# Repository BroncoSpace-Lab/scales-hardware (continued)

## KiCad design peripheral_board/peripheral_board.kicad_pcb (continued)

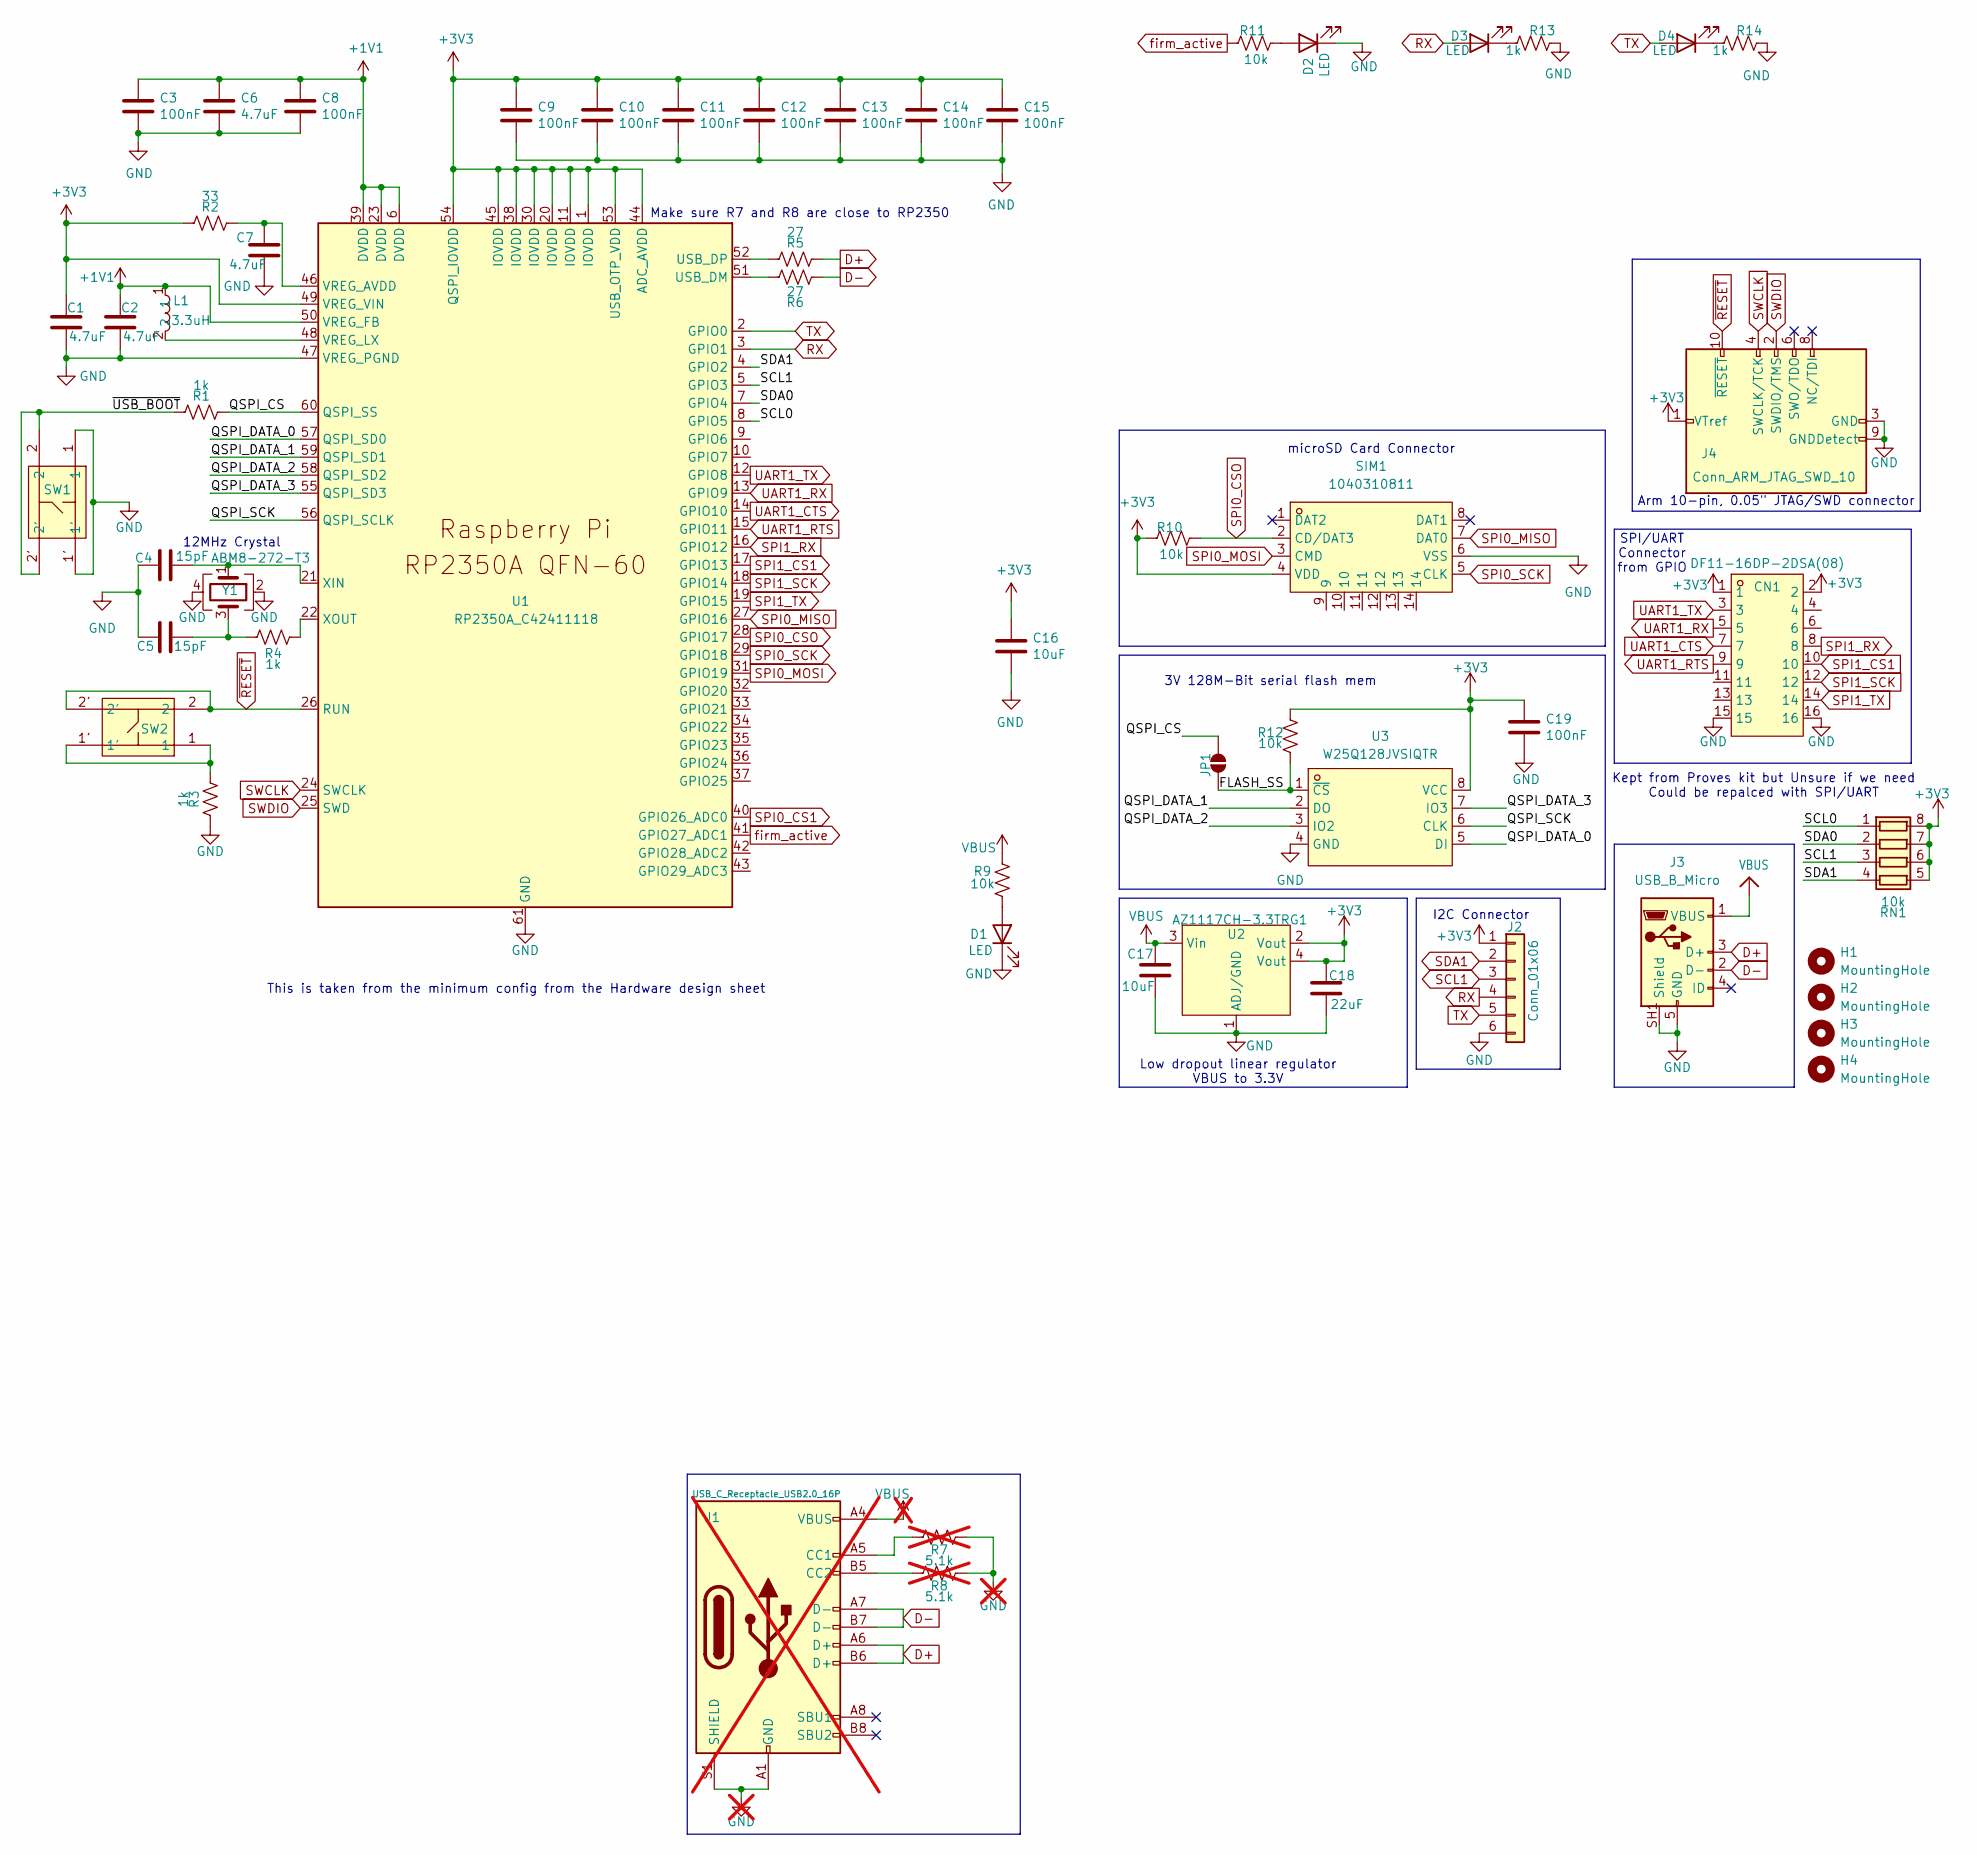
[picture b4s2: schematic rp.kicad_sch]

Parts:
C1, C2: 4.7uF; C_0402_1005Metric_small_pads
C3, C8, C9, C10, C11, C12, C13, C14, C15, C19: 100nF; C_0402_1005Metric
C4, C5: 15pF; C_0402_1005Metric
C6, C7: 4.7uF; C_0402_1005Metric
C16, C17: 10uF; C_0805_2012Metric
C18: 22uF; C_0805_2012Metric
CN1: DF11-16DP-2DSA(08); CONN-TH_DF11-16DP-2DSA-08; LCSC Part C530981
D1, D2, D3, D4: LED; LED_0603_1608Metric
H1, H2, H3, H4: MountingHole; MountingHole_2.5mm
J1: USB_C_Receptacle_USB2.0_16P; USB_C_Receptacle_HRO_TYPE-C-31-M-12; not fitted
J2: Conn_01x06; HDR-TH_6P-P2.54-V-M-1
J3: USB_B_Micro; MICRO-USB-SMD_5P-P0.65-H-F_105164-0001
J4: Conn_ARM_JTAG_SWD_10; JTAG_2X05_1.27MM_BOX_NOCREAM
JP1: SolderJumper_2_Open; SolderJumper-2_P1.3mm_Open_RoundedPad1.0x1.5mm
L1: 3.3uH; IND-SMD_L2.0-W1.6_AOTA-B201610S3R3-101-T; LCSC Part C42411119
R1, R3, R4: 1k; R_0402_1005Metric
R2: 33; R_0402_1005Metric
R5, R6: 27; R_0402_1005Metric
R7, R8: 5.1k; R_0603_1608Metric; not fitted
R9, R10, R11, R12: 10k; R_0603_1608Metric
R13, R14: 1k; R_0603_1608Metric
RN1: 10k; R_Array_Convex_4x0603
SIM1: 1040310811; SIM-SMD_8P-1040310811; LCSC Part C585350
SW1, SW2: EVPAA602W; KEY-TH_4P-L3.5-W4.9-P2.80-LS4.3; LCSC Part C79148
U1: RP2350A_C42411118; QFN-60_L7.0-W7.0-P0.40-TL-EP3.4; LCSC Part C42411118
U2: AZ1117CH-3.3TRG1; SOT-223-3_L6.5-W3.4-P2.30-LS7.0-BR; LCSC Part C92102
U3: W25Q128JVSIQTR; SOIC-8_L5.3-W5.3-P1.27-LS8.0-BL; LCSC Part C97521
Y1: ABM8-272-T3; Crystal_SMD_3225-4Pin_3.2x2.5mm

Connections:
+1V1: C2.1, C3.1, C6.1, C8.1, L1.1, U1.6 (DVDD), U1.23 (DVDD), U1.39 (DVDD), U1.50 (VREG_FB)
+3V3: C1.1, C9.1, C10.1, C11.1, C12.1, C13.1, C14.1, C15.1, C16.1, C18.2, C19.1, CN1.1, CN1.2, J2.1, J4.1 (VTref), R2.2, R10.2, R12.2, RN1.5 (R4.2), RN1.6 (R3.2), RN1.7 (R2.2), RN1.8 (R1.2), SIM1.4 (VDD), U1.1 (IOVDD), U1.11 (IOVDD), U1.20 (IOVDD), U1.30 (IOVDD), U1.38 (IOVDD), U1.44 (ADC_AVDD), U1.45 (IOVDD), U1.49 (VREG_VIN), U1.53 (USB_OTP_VDD), U1.54 (QSPI_IOVDD), U2.2 (Vout), U2.4 (Vout), U3.8 (VCC); also elsewhere on the board
/Raspberry_pi/ QSPI_CS: JP1.1 (A), R1.1, U1.60 (QSPI_SS)
/Raspberry_pi/FLASH_SS: JP1.2 (B), R12.1, U3.1 (~CS)
/Raspberry_pi/QSPI_DATA_0: U1.57 (QSPI_SD0), U3.5 (DI)
/Raspberry_pi/QSPI_DATA_1: U1.59 (QSPI_SD1), U3.2 (DO)
/Raspberry_pi/QSPI_DATA_2: U1.58 (QSPI_SD2), U3.3 (IO2)
/Raspberry_pi/QSPI_DATA_3: U1.55 (QSPI_SD3), U3.7 (IO3)
/Raspberry_pi/QSPI_SCK: U1.56 (QSPI_SCLK), U3.6 (CLK)
/Raspberry_pi/SCL0: RN1.1 (R1.1), U1.8 (GPIO5)
/Raspberry_pi/SDA0: RN1.2 (R2.1), U1.7 (GPIO4)
/Raspberry_pi/~USB_BOOT: R1.2, SW1.2, SW1.2'
D+: J1.A6 (D+), J1.B6 (D+), J3.3 (D+), R5.1
D-: J1.A7 (D-), J1.B7 (D-), J3.2 (D-), R6.1
GND: C1.2, C2.2, C3.2, C4.1, C5.1, C6.2, C7.2, C8.2, C9.2, C10.2, C11.2, C12.2, C13.2, C14.2, C15.2, C16.2, C17.1, C18.1, C19.2, CN1.15, CN1.16, D1.1 (K), D2.1 (K), J1.A1 (GND), J1.A12 (GND), J1.B1 (GND), J1.B12 (GND), J1.S1 (SHIELD), J2.6, J3.5 (GND), J3.SH1 (Shield), J4.3 (GND), J4.5 (GND), J4.9 (GNDDetect), R3.2, R7.1, R8.1, R13.2, R14.2, SIM1.6 (VSS), SW1.1, SW1.1', U1.47 (VREG_PGND), U1.61 (GND), U2.1 (ADJ/GND), U3.4 (GND), Y1.2, Y1.4; also elsewhere on the board
unnamed: C5.2, R4.1, Y1.3
unnamed: D1.2 (A), R9.1
unnamed: D2.2 (A), R11.1
unnamed: D3.1 (K), R13.1
unnamed: D4.1 (K), R14.1
unnamed: J1.A5 (CC1), R7.2
unnamed: J1.B5 (CC2), R8.2
unnamed: R3.1, SW2.1, SW2.1'
unnamed: R6.2, U1.51 (USB_DM)
unnamed: R5.2, U1.52 (USB_DP)
unnamed: C7.1, R2.1, U1.46 (VREG_AVDD)
unnamed: L1.2, U1.48 (VREG_LX)
unnamed: C4.2, U1.21 (XIN), Y1.1
unnamed: R4.2, U1.22 (XOUT)
RX: D3.2 (A), J2.4, U1.3 (GPIO1)
SCL1: J2.3, RN1.3 (R3.1), U1.5 (GPIO3)
SDA1: J2.2, RN1.4 (R4.1), U1.4 (GPIO2)
SPI0_CS1: U1.40 (GPIO26_ADC0); also elsewhere on the board
SPI0_CSO: R10.1, SIM1.2 (CD/DAT3), U1.28 (GPIO17)
SPI0_MISO: SIM1.7 (DAT0), U1.27 (GPIO16); also elsewhere on the board
SPI0_MOSI: SIM1.3 (CMD), U1.31 (GPIO19); also elsewhere on the board
SPI0_SCK: SIM1.5 (CLK), U1.29 (GPIO18); also elsewhere on the board
SPI1_CS1: CN1.10, U1.17 (GPIO13)
SPI1_RX: CN1.8, U1.16 (GPIO12)
SPI1_SCK: CN1.12, U1.18 (GPIO14)
SPI1_TX: CN1.14, U1.19 (GPIO15)
SWCLK: J4.4 (SWCLK/TCK), U1.24 (SWCLK)
SWDIO: J4.2 (SWDIO/TMS), U1.25 (SWD)
TX: D4.2 (A), J2.5, U1.2 (GPIO0)
UART1_CTS: CN1.7, U1.14 (GPIO10)
UART1_RTS: CN1.9, U1.15 (GPIO11)
UART1_RX: CN1.5, U1.13 (GPIO9)
UART1_TX: CN1.3, U1.12 (GPIO8)
VBUS: C17.2, J1.A4 (VBUS), J1.A9 (VBUS), J1.B4 (VBUS), J1.B9 (VBUS), J3.1 (VBUS), R9.2, U2.3 (Vin); also elsewhere on the board
firm_active: R11.2, U1.41 (GPIO27_ADC1)
~RESET: J4.10 (~RESET), SW2.2, SW2.2', U1.26 (RUN)

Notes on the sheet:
12MHz Crystal
Low dropout linear regulator VBUS to 3.3V
Kept from Proves kit but Unsure if we need Could be repalced with SPI/UART
3V 128M-Bit serial flash mem
Make sure R7 and R8 are close to RP2350
microSD Card Connector
Arm 10-pin, 0.05" JTAG/SWD connector
This is taken from the minimum config from the Hardware design sheet
I2C Connector
SPI/UART Connector from GPIO

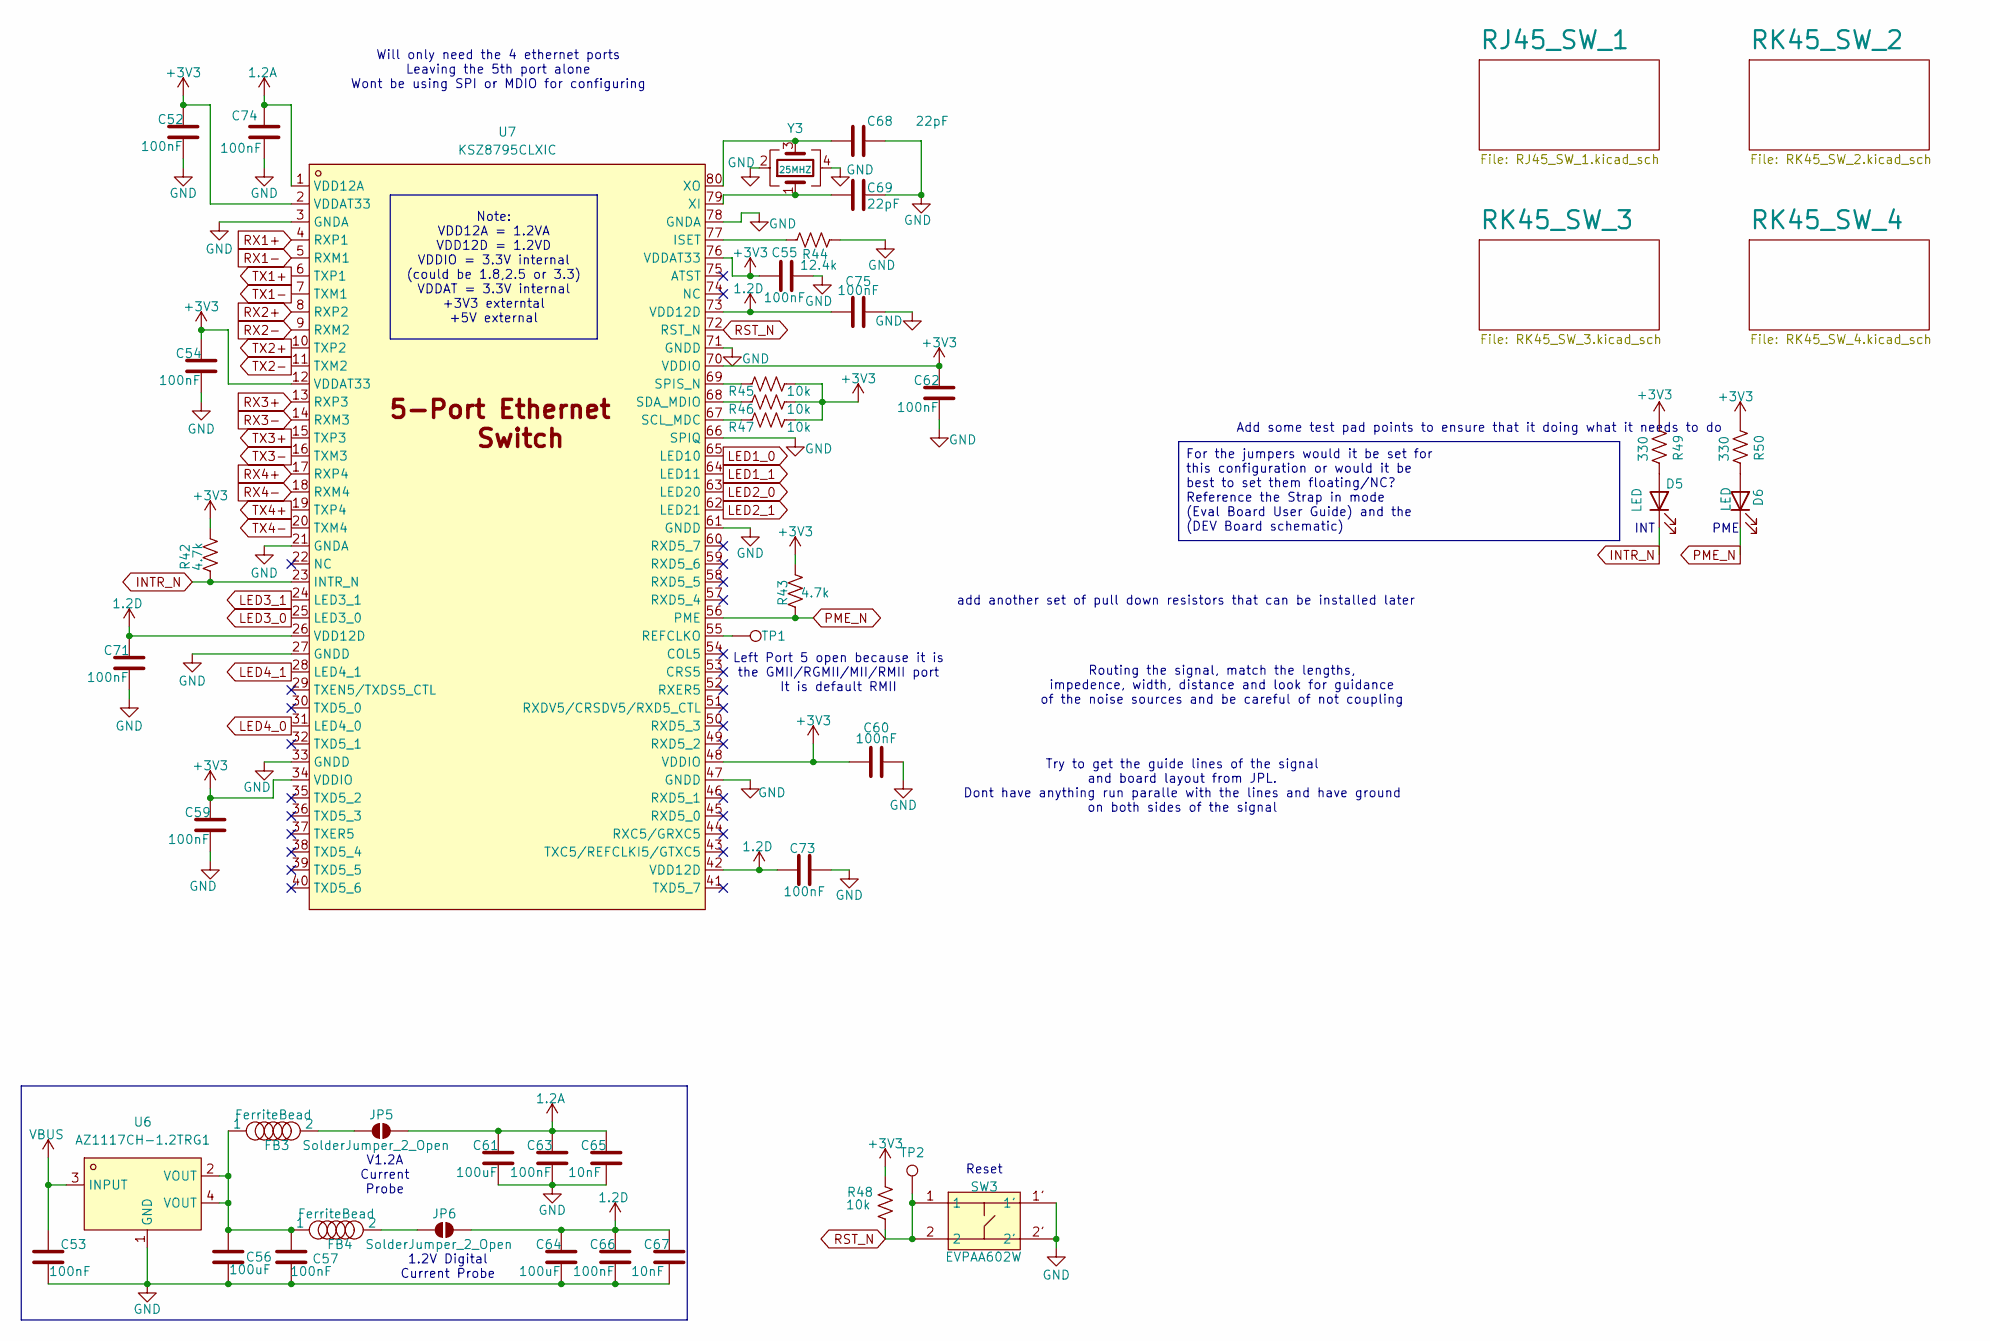
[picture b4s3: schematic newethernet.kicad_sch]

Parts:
C52, C53, C54, C55, C57, C59, C60, C62, C63, C66, C71, C73, C74, C75: 100nF; C_0402_1005Metric
C56, C61, C64: 100uF; C_0805_2012Metric
C65, C67: 10nF; C_0402_1005Metric
C68, C69: 22pF; C_0402_1005Metric
D5, D6: LED; LED_0603_1608Metric
FB3, FB4: FerriteBead; L_0603_1608Metric
JP5, JP6: SolderJumper_2_Open; SolderJumper-2_P1.3mm_Open_RoundedPad1.0x1.5mm
R42, R43: 4.7k; R_0603_1608Metric
R44: 12.4k; R_0603_1608Metric
R45, R46, R47: 10k; R_0402_1005Metric
R48: 10k; R_0603_1608Metric
R49, R50: 330; R_0603_1608Metric
SW3: EVPAA602W; KEY-TH_4P-L3.5-W4.9-P2.80-LS4.3; LCSC Part C79148
TP1, TP2: TestPoint; TestPoint_Pad_1.0x1.0mm
U6: AZ1117CH-1.2TRG1; SOT-223-3_L6.5-W3.4-P2.30-LS7.0-BR; LCSC Part C507895
U7: KSZ8795CLXIC; LQFP-80_L10.0-W10.0-P0.40-LS12.2-BL; LCSC Part C69416
Y3: 25MHZ; CRYSTAL-SMD_4P-L3.2-W2.5-BL

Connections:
1.2A: C61.2, C63.2, C65.2, C74.2, JP5.1 (A), U7.1 (VDD12A)
1.2D: C64.2, C66.2, C67.2, C71.2, C73.2, C75.2, JP6.1 (A), U7.26 (VDD12D), U7.42 (VDD12D), U7.73 (VDD12D)
+3V3: C52.2, C54.2, C55.2, C59.2, C60.2, C62.2, R42.1, R43.1, R45.2, R46.2, R47.2, R48.1, R49.2, R50.2, U7.2 (VDDAT33), U7.12 (VDDAT33), U7.34 (VDDIO), U7.48 (VDDIO), U7.70 (VDDIO), U7.76 (VDDAT33); also elsewhere on the board
GND: C52.1, C53.1, C54.1, C55.1, C56.1, C57.1, C59.1, C60.1, C61.1, C62.1, C63.1, C64.1, C65.1, C66.1, C67.1, C68.2, C69.2, C71.1, C73.1, C74.1, C75.1, R44.2, SW3.1', SW3.2', U6.1 (GND), U7.3 (GNDA), U7.21 (GNDA), U7.27 (GNDD), U7.33 (GNDD), U7.47 (GNDD), U7.61 (GNDD), U7.66 (SPIQ), U7.71 (GNDD), U7.78 (GNDA), Y3.2, Y3.4; also elsewhere on the board
INTR_N: D5.1 (K), R42.2, U7.23 (INTR_N)
LED1_0: U7.65 (LED10); also elsewhere on the board
LED1_1: U7.64 (LED11); also elsewhere on the board
LED2_0: U7.63 (LED20); also elsewhere on the board
LED2_1: U7.62 (LED21); also elsewhere on the board
LED3_0: U7.25 (LED3_0); also elsewhere on the board
LED3_1: U7.24 (LED3_1); also elsewhere on the board
LED4_0: U7.31 (LED4_0); also elsewhere on the board
LED4_1: U7.28 (LED4_1); also elsewhere on the board
unnamed: C56.2, C57.2, FB3.1, FB4.1, U6.2 (VOUT), U6.4 (VOUT)
unnamed: D5.2 (A), R49.1
unnamed: D6.2 (A), R50.1
unnamed: FB3.2, JP5.2 (B)
unnamed: FB4.2, JP6.2 (B)
unnamed: R44.1, U7.77 (ISET)
unnamed: TP1.1, U7.55 (REFCLKO)
unnamed: R47.1, U7.67 (SCL_MDC)
unnamed: R46.1, U7.68 (SDA_MDIO)
unnamed: R45.1, U7.69 (SPIS_N)
unnamed: C69.1, U7.79 (XI), Y3.1
unnamed: C68.1, U7.80 (XO), Y3.3
PME_N: D6.1 (K), R43.2, U7.56 (PME)
RST_N: R48.2, SW3.1, SW3.2, TP2.1, U7.72 (RST_N)
RX1+: U7.4 (RXP1); also elsewhere on the board
RX1-: U7.5 (RXM1); also elsewhere on the board
RX2+: U7.8 (RXP2); also elsewhere on the board
RX2-: U7.9 (RXM2); also elsewhere on the board
RX3+: U7.13 (RXP3); also elsewhere on the board
RX3-: U7.14 (RXM3); also elsewhere on the board
RX4+: U7.17 (RXP4); also elsewhere on the board
RX4-: U7.18 (RXM4); also elsewhere on the board
TX1+: U7.6 (TXP1); also elsewhere on the board
TX1-: U7.7 (TXM1); also elsewhere on the board
TX2+: U7.10 (TXP2); also elsewhere on the board
TX2-: U7.11 (TXM2); also elsewhere on the board
TX3+: U7.15 (TXP3); also elsewhere on the board
TX3-: U7.16 (TXM3); also elsewhere on the board
TX4+: U7.19 (TXP4); also elsewhere on the board
TX4-: U7.20 (TXM4); also elsewhere on the board
VBUS: C53.2, U6.3 (INPUT); also elsewhere on the board

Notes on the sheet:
Routing the signal, match the lengths, impedence, width, distance and look for guidance of the noise sources and be careful of not coupling
1.2V Digital Current Probe
add another set of pull down resistors that can be installed later
Try to get the guide lines of the signal and board layout from JPL. Dont have anything run paralle with the lines and have ground on both sides of the signal
INT
V1.2A Current Probe
Reset
Will only need the 4 ethernet ports Leaving the 5th port alone Wont be using SPI or MDIO for configuring
Left Port 5 open because it is the GMII/RGMII/MII/RMII port It is default RMII
Add some test pad points to ensure that it doing what it needs to do
PME
For the jumpers would it be set for this configuration or would it be best to set them floating/NC? Reference the Strap in mode (Eval Board User Guide) and the (DEV Board schematic)
Note: VDD12A = 1.2VA VDD12D = 1.2VD VDDIO = 3.3V internal (could be 1.8,2.5 or 3.3) VDDAT = 3.3V internal +3V3 externtal +5V external

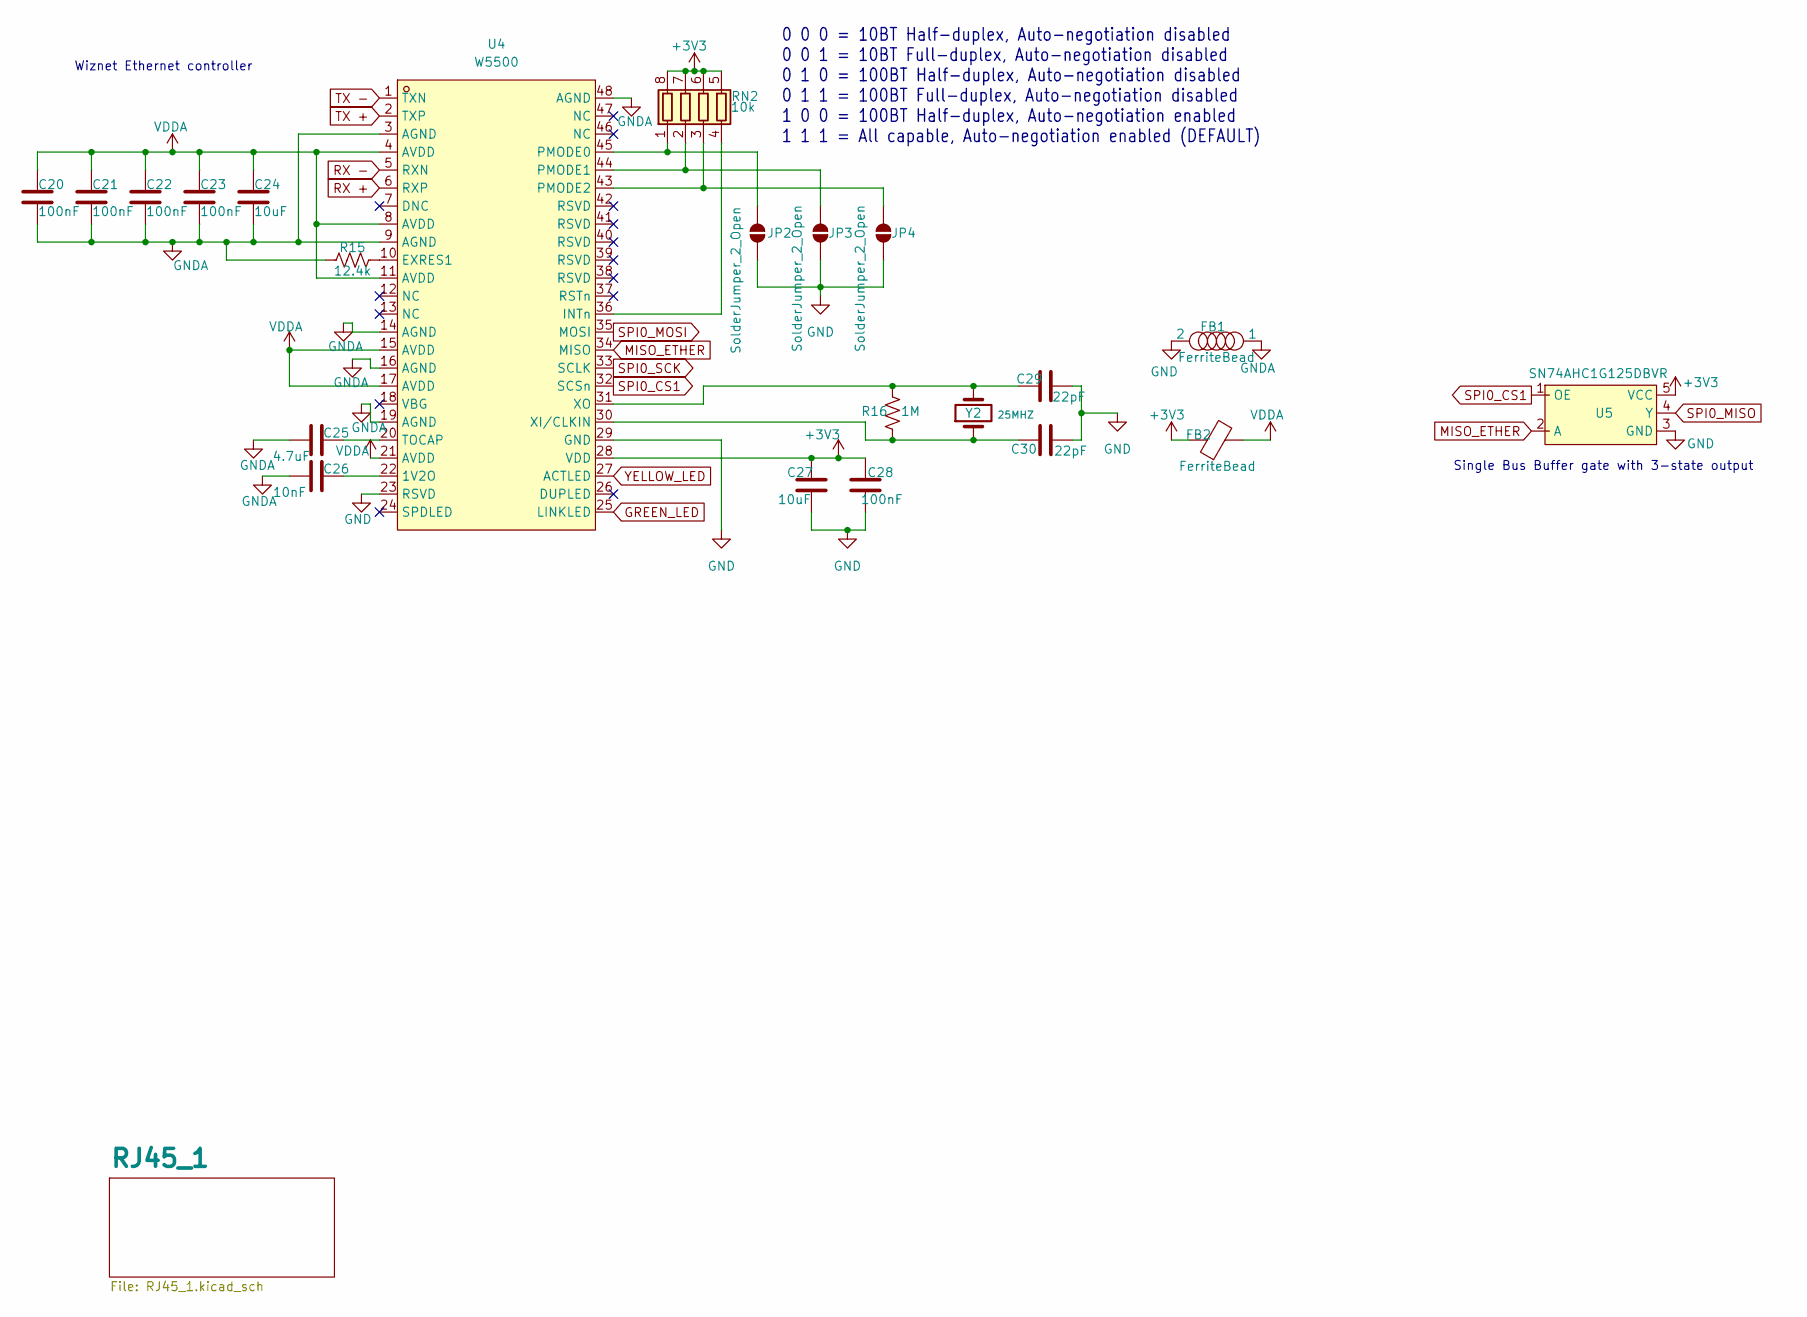
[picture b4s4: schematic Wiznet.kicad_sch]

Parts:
C20, C21, C22, C23, C28: 100nF; C_0402_1005Metric
C24, C27: 10uF; C_0402_1005Metric
C25: 4.7uF; C_0402_1005Metric
C26: 10nF; C_0402_1005Metric
C29, C30: 22pF; C_0402_1005Metric
FB1, FB2: FerriteBead; L_0603_1608Metric
JP2, JP3, JP4: SolderJumper_2_Open; SolderJumper-2_P1.3mm_Open_RoundedPad1.0x1.5mm
R15: 12.4k; R_0603_1608Metric
R16: 1M; R_0603_1608Metric
RN2: 10k; R_Array_Convex_4x0603
U4: W5500; LQFP-48_L7.0-W7.0-P0.50-LS9.0-BL; LCSC Part C32843
U5: SN74AHC1G125DBVR; SOT-23-5_L3.0-W1.7-P0.95-LS2.8-BR; LCSC Part C7468
Y2: 25MHZ; Crystal_SMD_3225-4Pin_3.2x2.5mm

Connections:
+3V3: C27.2, C28.2, FB2.1, RN2.5 (R4.2), RN2.6 (R3.2), RN2.7 (R2.2), RN2.8 (R1.2), U4.28 (VDD), U5.5 (VCC); also elsewhere on the board
GND: C27.1, C28.1, C29.1, C30.1, FB1.2, JP2.1 (A), JP3.1 (A), JP4.1 (A), U4.23 (RSVD), U4.29 (GND), U5.3 (GND); also elsewhere on the board
GNDA: C20.1, C21.1, C22.1, C23.1, C24.1, C25.2, C26.2, FB1.1, R15.1, U4.3 (AGND), U4.9 (AGND), U4.14 (AGND), U4.16 (AGND), U4.19 (AGND), U4.48 (AGND); also elsewhere on the board
GREEN_LED: U4.25 (LINKLED); also elsewhere on the board
MISO_ETHER: U4.34 (MISO), U5.2 (A)
unnamed: JP2.2 (B), RN2.1 (R1.1), U4.45 (PMODE0)
unnamed: JP3.2 (B), RN2.2 (R2.1), U4.44 (PMODE1)
unnamed: JP4.2 (B), RN2.3 (R3.1), U4.43 (PMODE2)
unnamed: RN2.4 (R4.1), U4.36 (INTn)
unnamed: C26.1, U4.22 (1V2O)
unnamed: R15.2, U4.10 (EXRES1)
unnamed: C25.1, U4.20 (TOCAP)
unnamed: C30.2, R16.1, U4.30 (XI/CLKIN), Y2.1
unnamed: C29.2, R16.2, U4.31 (XO), Y2.3 (2)
RX +: U4.6 (RXP); also elsewhere on the board
RX -: U4.5 (RXN); also elsewhere on the board
SPI0_CS1: U4.32 (SCSn), U5.1 (OE); also elsewhere on the board
SPI0_MISO: U5.4 (Y); also elsewhere on the board
SPI0_MOSI: U4.35 (MOSI); also elsewhere on the board
SPI0_SCK: U4.33 (SCLK); also elsewhere on the board
TX +: U4.2 (TXP); also elsewhere on the board
TX -: U4.1 (TXN); also elsewhere on the board
VDDA: C20.2, C21.2, C22.2, C23.2, C24.2, FB2.2, U4.4 (AVDD), U4.8 (AVDD), U4.11 (AVDD), U4.15 (AVDD), U4.17 (AVDD), U4.21 (AVDD); also elsewhere on the board
YELLOW_LED: U4.27 (ACTLED); also elsewhere on the board

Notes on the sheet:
Wiznet Ethernet controller
Single Bus Buffer gate with 3-state output
0 0 0 = 10BT Half-duplex, Auto-negotiation disabled 0 0 1 = 10BT Full-duplex, Auto-negotiation disabled 0 1 0 = 100BT Half-duplex, Auto-negotiation disabled 0 1 1 = 100BT Full-duplex, Auto-negotiation disabled 1 0 0 = 100BT Half-duplex, Auto-negotiation enabled 1 1 1 = All capable, Auto-negotiation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

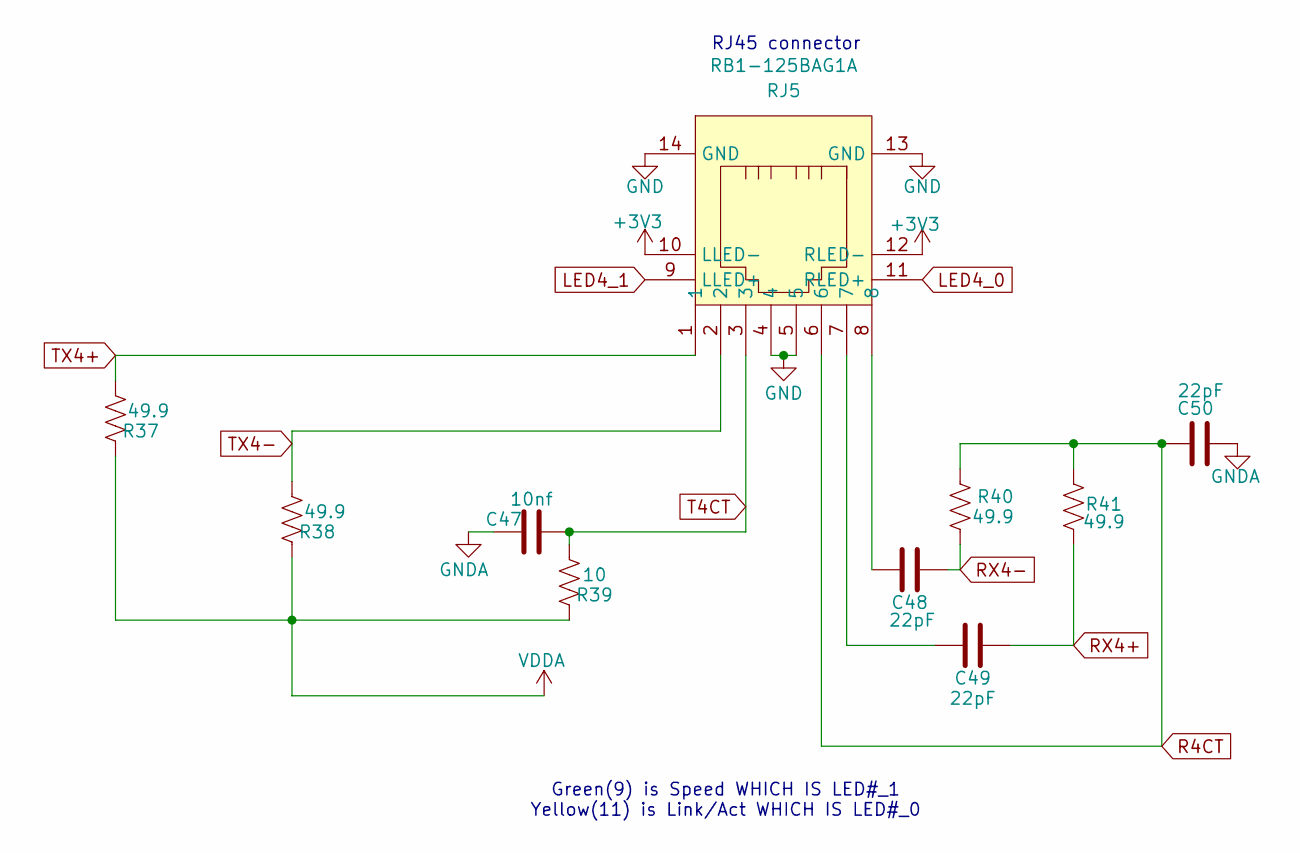
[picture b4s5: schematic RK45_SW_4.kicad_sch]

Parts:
C47: 10nf; C_0402_1005Metric
C48, C49, C50: 22pF; C_0402_1005Metric
R37, R38, R40, R41: 49.9; R_0603_1608Metric
R39: 10; R_0603_1608Metric
RJ5: RB1-125BAG1A; RJ45-TH_RB1-125BAG1A; LCSC Part C910370

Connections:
+3V3: RJ5.10 (LLED-), RJ5.12 (RLED-); also elsewhere on the board
GND: RJ5.4, RJ5.5, RJ5.13 (GND), RJ5.14 (GND); also elsewhere on the board
GNDA: C47.1, C50.1; also elsewhere on the board
LED4_0: RJ5.11 (RLED+); also elsewhere on the board
LED4_1: RJ5.9 (LLED+); also elsewhere on the board
unnamed: C48.2, RJ5.8
unnamed: C49.2, RJ5.7
R4CT: C50.2, R40.1, R41.1, RJ5.6
RX4+: C49.1, R41.2; also elsewhere on the board
RX4-: C48.1, R40.2; also elsewhere on the board
T4CT: C47.2, R39.1, RJ5.3
TX4+: R37.1, RJ5.1; also elsewhere on the board
TX4-: R38.1, RJ5.2; also elsewhere on the board
VDDA: R37.2, R38.2, R39.2; also elsewhere on the board

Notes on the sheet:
Green(9) is Speed WHICH IS LED#_1 Yellow(11) is Link/Act WHICH IS LED#_0
RJ45 connector

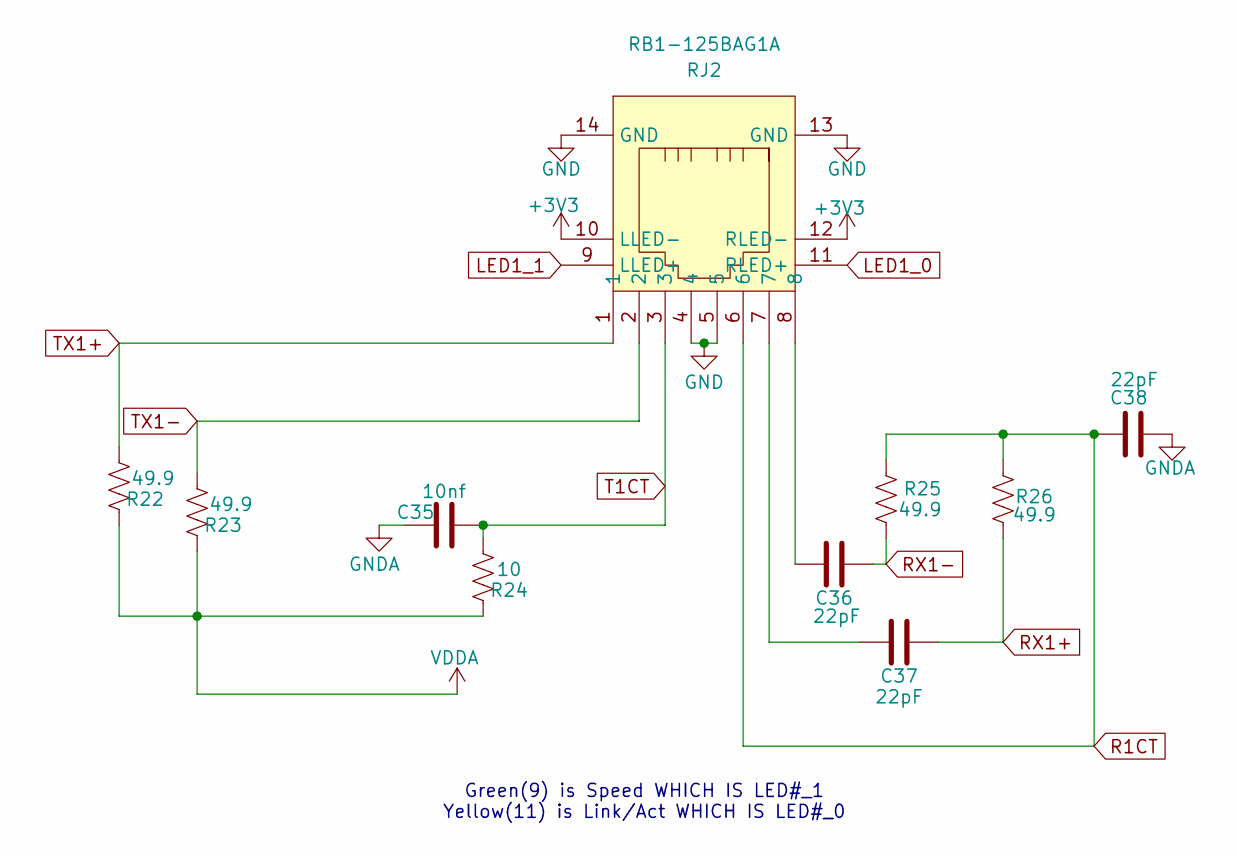
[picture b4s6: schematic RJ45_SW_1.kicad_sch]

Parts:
C35: 10nf; C_0402_1005Metric
C36, C37, C38: 22pF; C_0402_1005Metric
R22, R23, R25, R26: 49.9; R_0603_1608Metric
R24: 10; R_0603_1608Metric
RJ2: RB1-125BAG1A; RJ45-TH_RB1-125BAG1A; LCSC Part C910370

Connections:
+3V3: RJ2.10 (LLED-), RJ2.12 (RLED-); also elsewhere on the board
GND: RJ2.4, RJ2.5, RJ2.13 (GND), RJ2.14 (GND); also elsewhere on the board
GNDA: C35.1, C38.1; also elsewhere on the board
LED1_0: RJ2.11 (RLED+); also elsewhere on the board
LED1_1: RJ2.9 (LLED+); also elsewhere on the board
unnamed: C36.2, RJ2.8
unnamed: C37.2, RJ2.7
R1CT: C38.2, R25.1, R26.1, RJ2.6
RX1+: C37.1, R26.2; also elsewhere on the board
RX1-: C36.1, R25.2; also elsewhere on the board
T1CT: C35.2, R24.1, RJ2.3
TX1+: R22.1, RJ2.1; also elsewhere on the board
TX1-: R23.1, RJ2.2; also elsewhere on the board
VDDA: R22.2, R23.2, R24.2; also elsewhere on the board

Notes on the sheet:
Green(9) is Speed WHICH IS LED#_1 Yellow(11) is Link/Act WHICH IS LED#_0

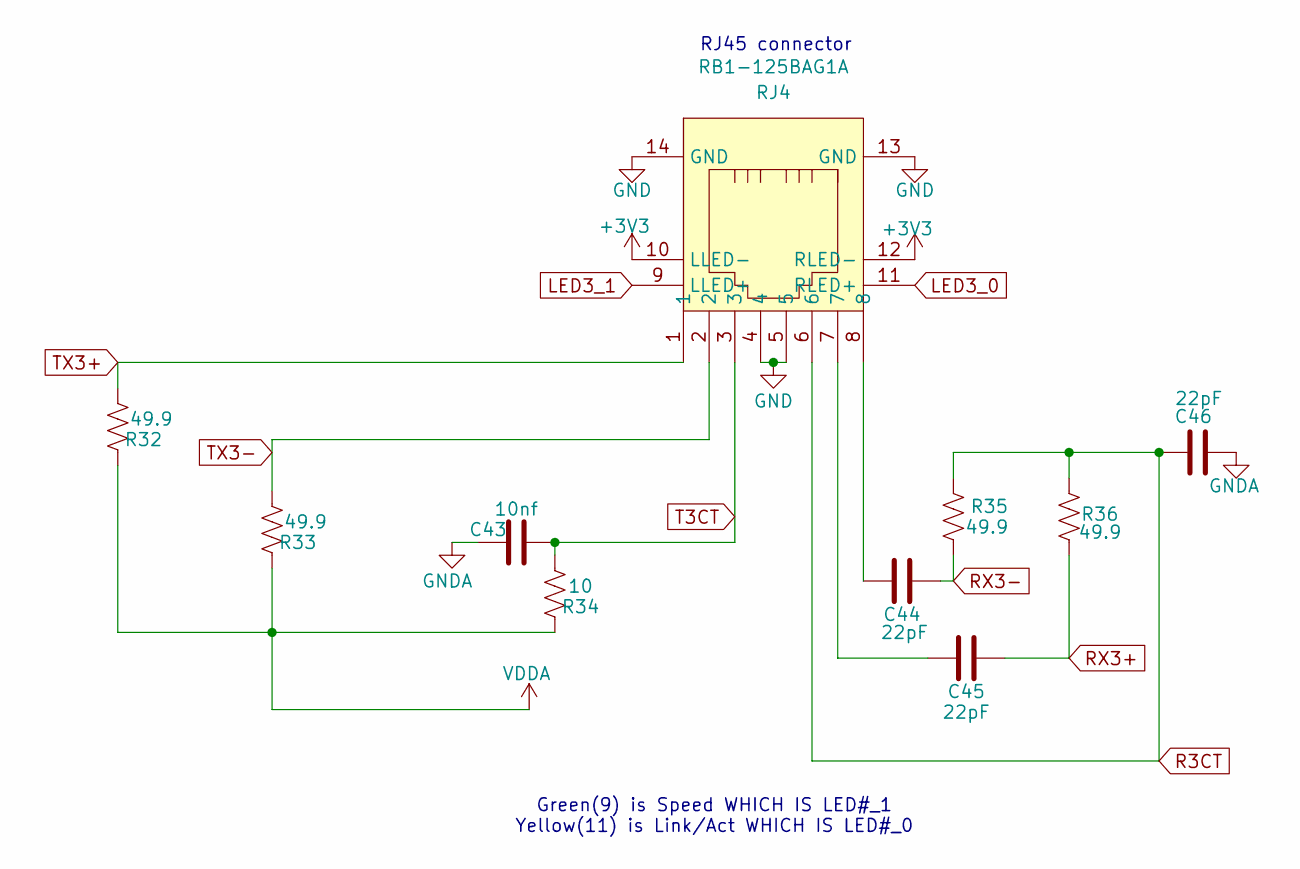
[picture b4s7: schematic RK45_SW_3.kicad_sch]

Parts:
C43: 10nf; C_0402_1005Metric
C44, C45, C46: 22pF; C_0402_1005Metric
R32, R33, R35, R36: 49.9; R_0603_1608Metric
R34: 10; R_0603_1608Metric
RJ4: RB1-125BAG1A; RJ45-TH_RB1-125BAG1A; LCSC Part C910370

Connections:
+3V3: RJ4.10 (LLED-), RJ4.12 (RLED-); also elsewhere on the board
GND: RJ4.4, RJ4.5, RJ4.13 (GND), RJ4.14 (GND); also elsewhere on the board
GNDA: C43.1, C46.1; also elsewhere on the board
LED3_0: RJ4.11 (RLED+); also elsewhere on the board
LED3_1: RJ4.9 (LLED+); also elsewhere on the board
unnamed: C44.2, RJ4.8
unnamed: C45.2, RJ4.7
R3CT: C46.2, R35.1, R36.1, RJ4.6
RX3+: C45.1, R36.2; also elsewhere on the board
RX3-: C44.1, R35.2; also elsewhere on the board
T3CT: C43.2, R34.1, RJ4.3
TX3+: R32.1, RJ4.1; also elsewhere on the board
TX3-: R33.1, RJ4.2; also elsewhere on the board
VDDA: R32.2, R33.2, R34.2; also elsewhere on the board

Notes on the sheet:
RJ45 connector
Green(9) is Speed WHICH IS LED#_1 Yellow(11) is Link/Act WHICH IS LED#_0

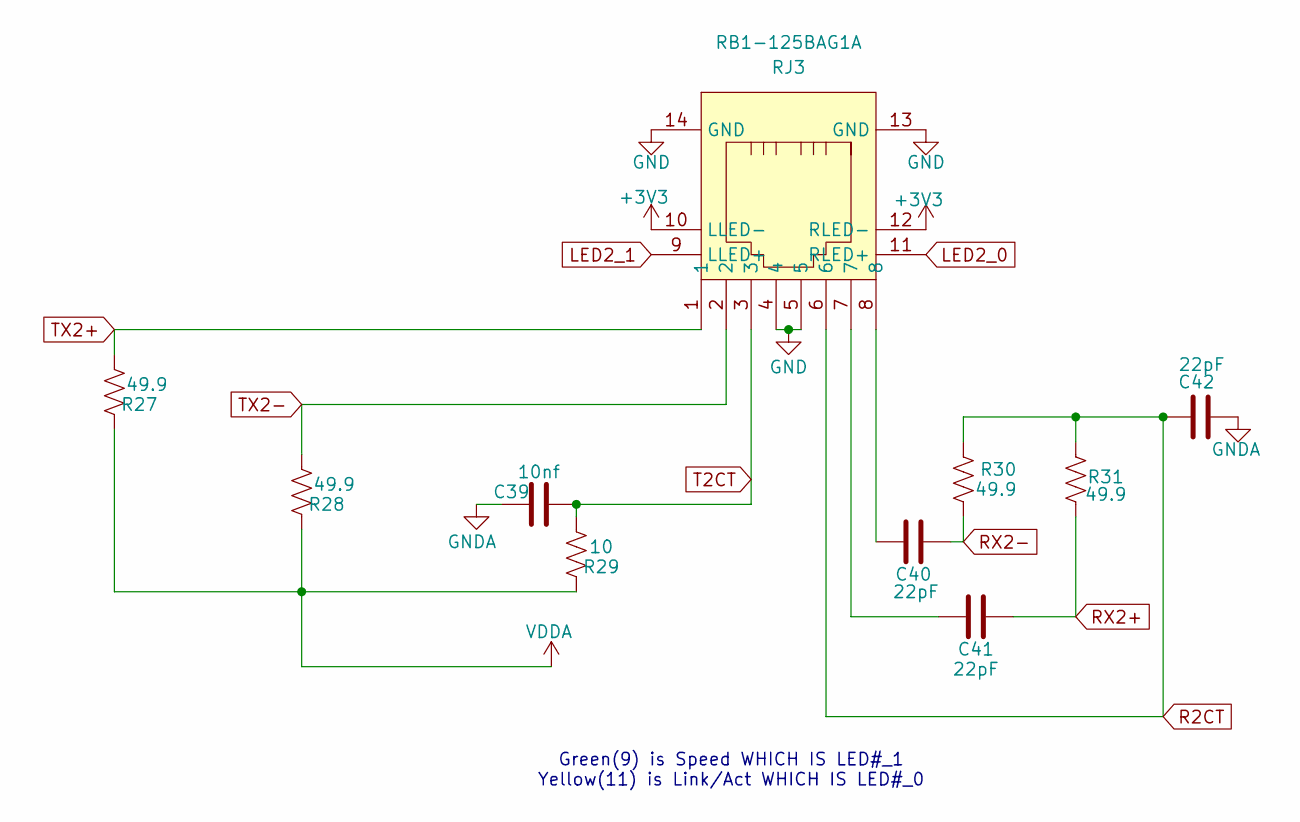
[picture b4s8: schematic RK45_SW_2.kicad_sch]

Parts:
C39: 10nf; C_0402_1005Metric
C40, C41, C42: 22pF; C_0402_1005Metric
R27, R28, R30, R31: 49.9; R_0603_1608Metric
R29: 10; R_0603_1608Metric
RJ3: RB1-125BAG1A; RJ45-TH_RB1-125BAG1A; LCSC Part C910370

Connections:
+3V3: RJ3.10 (LLED-), RJ3.12 (RLED-); also elsewhere on the board
GND: RJ3.4, RJ3.5, RJ3.13 (GND), RJ3.14 (GND); also elsewhere on the board
GNDA: C39.1, C42.1; also elsewhere on the board
LED2_0: RJ3.11 (RLED+); also elsewhere on the board
LED2_1: RJ3.9 (LLED+); also elsewhere on the board
unnamed: C40.2, RJ3.8
unnamed: C41.2, RJ3.7
R2CT: C42.2, R30.1, R31.1, RJ3.6
RX2+: C41.1, R31.2; also elsewhere on the board
RX2-: C40.1, R30.2; also elsewhere on the board
T2CT: C39.2, R29.1, RJ3.3
TX2+: R27.1, RJ3.1; also elsewhere on the board
TX2-: R28.1, RJ3.2; also elsewhere on the board
VDDA: R27.2, R28.2, R29.2; also elsewhere on the board

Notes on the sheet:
Green(9) is Speed WHICH IS LED#_1 Yellow(11) is Link/Act WHICH IS LED#_0

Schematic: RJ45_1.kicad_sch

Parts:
C31, C32, C33: 22pF; C_0402_1005Metric
C34: 10nF; C_0402_1005Metric
R17, R18, R20, R21: 49.9; R_0603_1608Metric
R19: 10; R_0603_1608Metric
RJ1: RB1-125BAG1A; RJ45-TH_RB1-125BAG1A; LCSC Part C910370

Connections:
+3V3: RJ1.10 (LLED-), RJ1.12 (RLED-); also elsewhere on the board
GND: RJ1.4, RJ1.5, RJ1.13 (GND), RJ1.14 (GND); also elsewhere on the board
GNDA: C31.1, C34.1; also elsewhere on the board
GREEN_LED: RJ1.9 (LLED+); also elsewhere on the board
unnamed: C32.2, RJ1.7
unnamed: C33.2, RJ1.8
RCT: C31.2, R17.1, R18.1, RJ1.6
RX +: C32.1, R17.2; also elsewhere on the board
RX -: C33.1, R18.2; also elsewhere on the board
TCT: C34.2, R19.1, RJ1.3
TX +: R21.1, RJ1.1; also elsewhere on the board
TX -: R20.1, RJ1.2; also elsewhere on the board
VDDA: R19.2, R20.2, R21.2; also elsewhere on the board
YELLOW_LED: RJ1.11 (RLED+); also elsewhere on the board

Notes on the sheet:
RJ45 connector
